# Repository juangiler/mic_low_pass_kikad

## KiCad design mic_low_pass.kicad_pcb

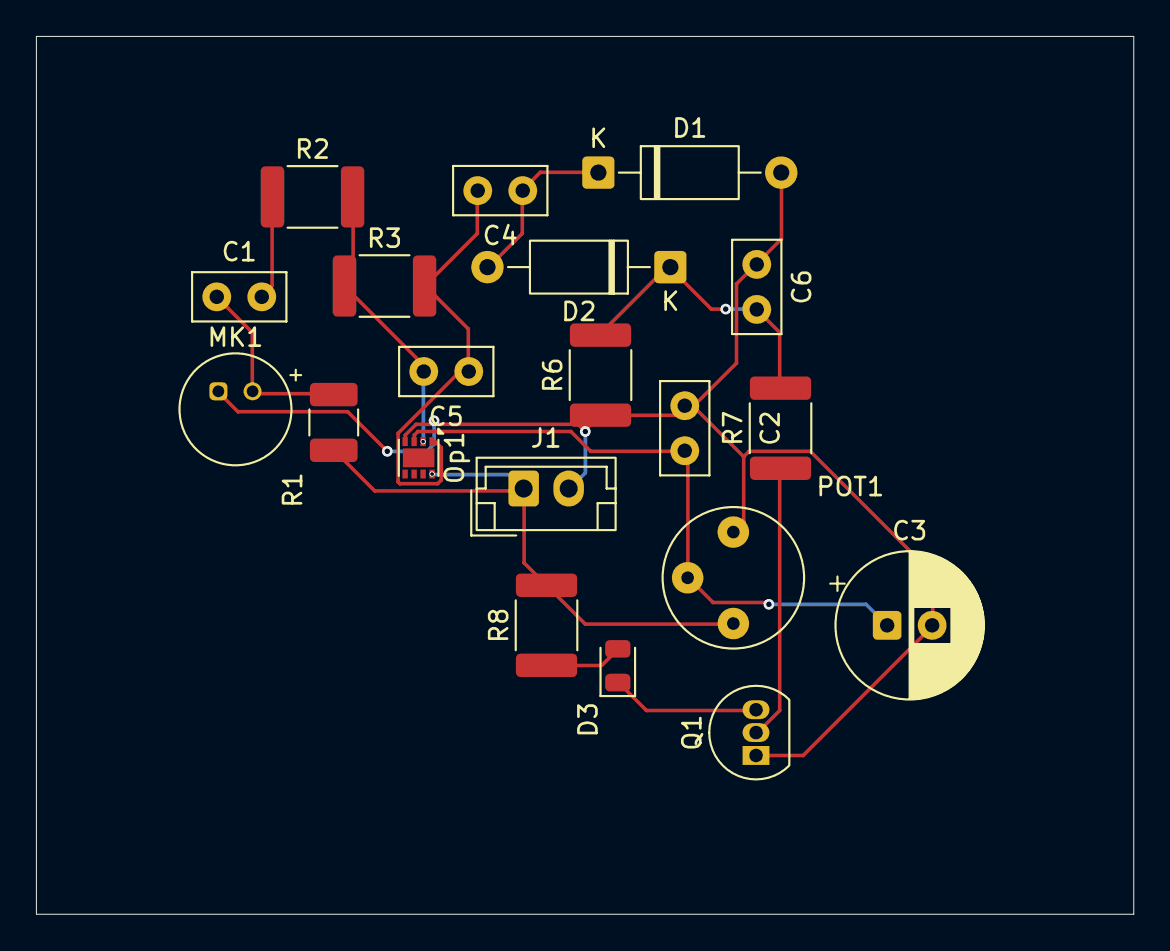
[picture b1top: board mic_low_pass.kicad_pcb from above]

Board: 2 copper layers, 61.0 x 48.8 mm, 20 parts (0 on the bottom side), 12 nets.

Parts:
C1: 100u; C_Disc_D5.0mm_W2.5mm_P2.50mm
C2, C4: 100n; C_Disc_D5.0mm_W2.5mm_P2.50mm
C3: 10u; CP_Radial_D8.0mm_P2.50mm
C5: 220p; C_Disc_D5.0mm_W2.5mm_P2.50mm
C6: 10u; C_Disc_D5.0mm_W2.5mm_P2.50mm
D1, D2: D; D_A-405_P10.16mm_Horizontal
D3: LED; LED_0805_2012Metric
J1: Conn_01x02_Pin; JST_EH_B2B-EH-A_1x02_P2.50mm_Vertical
MK1: Microphone_Condenser; POM-2244P-C3310-2-R
Op1: LM358_DFN_single; DFN-8-1EP_2x2mm_P0.5mm_EP1.05x1.75mm
POT1: 10k; Potentiometer_Bourns_3339P_Vertical_HandSoldering
Q1: 2N3904; TO-92_Inline
R1: 2.2k; R_1210_3225Metric_Pad1.30x2.65mm_HandSolder
R2: 2.2; R_1812_4532Metric_Pad1.30x3.40mm_HandSolder
R3: 1M; R_1812_4532Metric_Pad1.30x3.40mm_HandSolder
R6: 100k; R_1812_4532Metric_Pad1.30x3.40mm_HandSolder
R7: 470; R_1812_4532Metric_Pad1.30x3.40mm_HandSolder
R8: 330; R_1812_4532Metric_Pad1.30x3.40mm_HandSolder

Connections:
/Vclamp: C4.1, D1.1 (K), D2.2 (A)
/Vdet: C6.2, D2.1 (K), R6.2, R7.2
/Vin: C5.2, Op1.2 (-), R2.2, R3.1
/Vled: D3.1 (K), Q1.3 (C)
/Vr8: D3.2 (A), R8.1
GND: C2.1, C3.2, C6.1, D1.2 (A), J1.2, MK1.1 (-), Op1.4 (VEE), POT1.3, Q1.1 (E), R6.1
unnamed: C1.2, R2.1
unnamed: C1.1, MK1.2 (+), R1.2
Vfilter: C4.2, C5.1, Op1.1, R3.2
Vin+: J1.1, Op1.8 (VCC), POT1.1, R1.1, R8.2
Vout: Q1.2 (B), R7.1
Vref: C2.2, C3.1, Op1.3 (+), POT1.2
